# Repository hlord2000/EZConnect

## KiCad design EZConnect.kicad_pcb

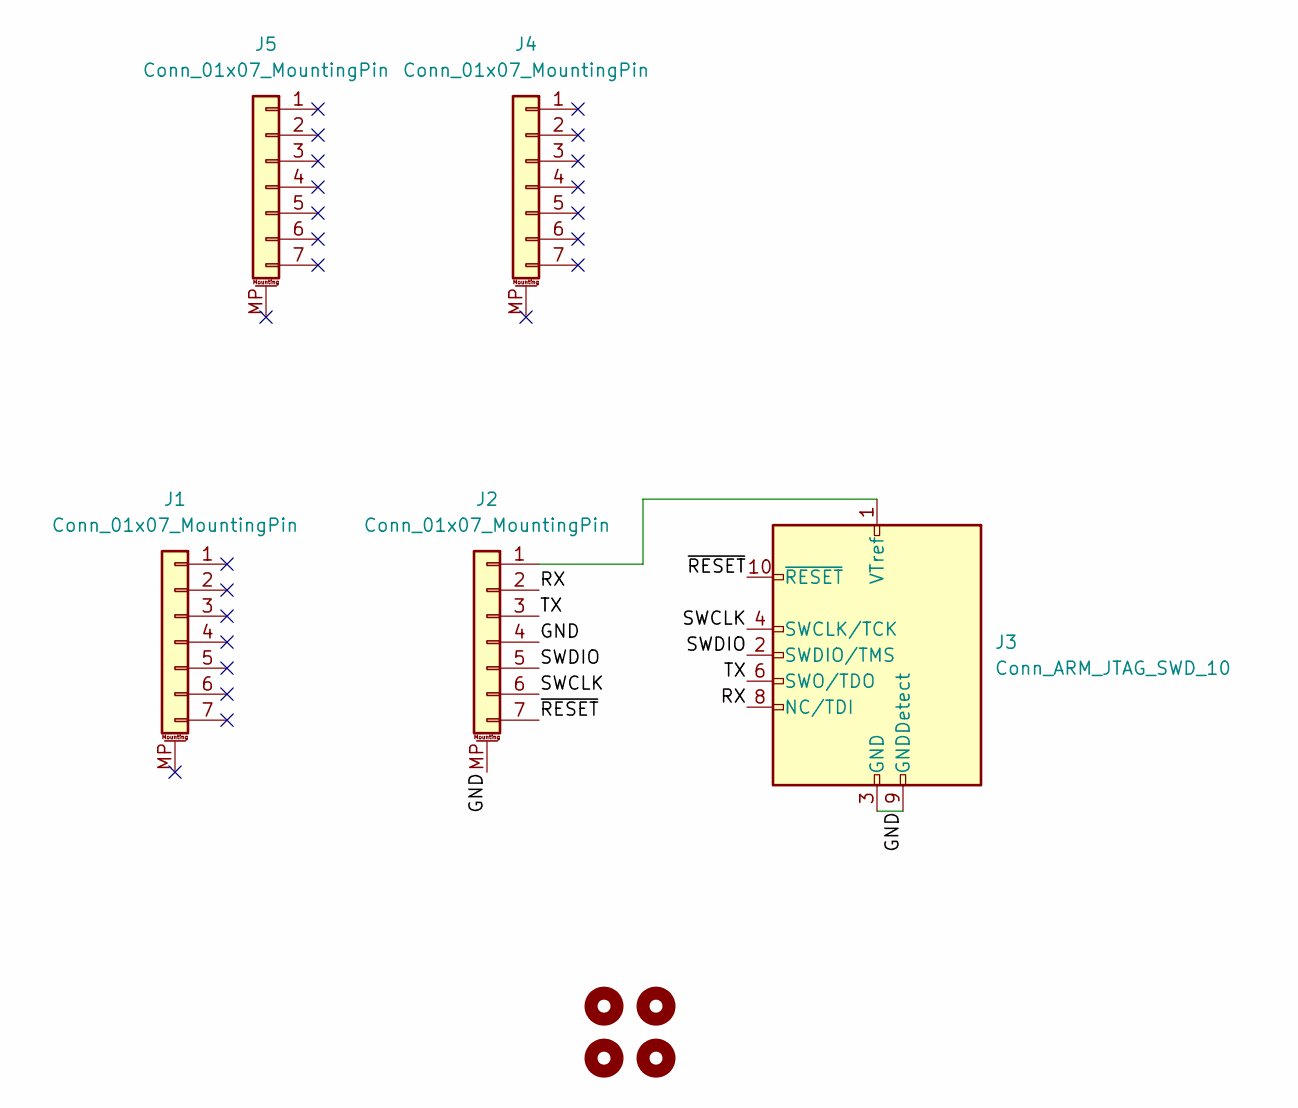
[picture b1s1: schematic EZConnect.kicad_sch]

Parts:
H1, H2, H3, H4: MountingHole; mousebites_2.5mm
J1, J2: Conn_01x07_MountingPin; EZConnect
J3: Conn_ARM_JTAG_SWD_10; PinHeader_2x05_P1.27mm_Vertical
J4, J5: Conn_01x07_MountingPin; EZConnect_Contact

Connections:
/GND: J2.4, J2.MP (MountPin), J3.3 (GND), J3.5 (GND), J3.9 (GNDDetect)
/RX: J2.2, J3.8 (NC/TDI)
/SWCLK: J2.6, J3.4 (SWCLK/TCK)
/SWDIO: J2.5, J3.2 (SWDIO/TMS)
/TX: J2.3, J3.6 (SWO/TDO)
/~RESET: J2.7, J3.10 (~RESET)
unnamed: J2.1, J3.1 (VTref)

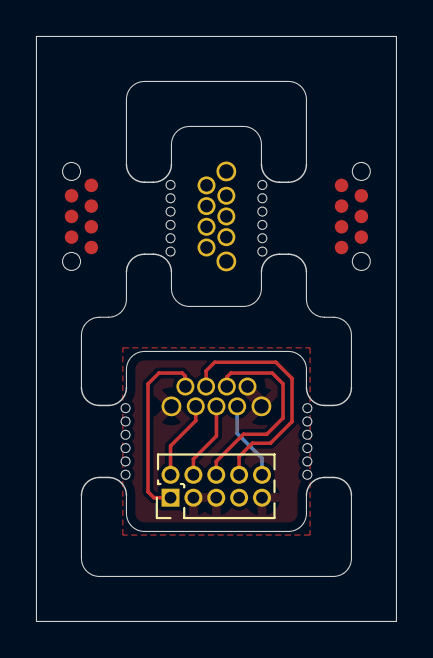
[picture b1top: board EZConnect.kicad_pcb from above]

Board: 2 copper layers, 20.0 x 32.5 mm, 9 parts (0 on the bottom side), 7 nets.

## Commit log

2024-12-24 Initial commit.
